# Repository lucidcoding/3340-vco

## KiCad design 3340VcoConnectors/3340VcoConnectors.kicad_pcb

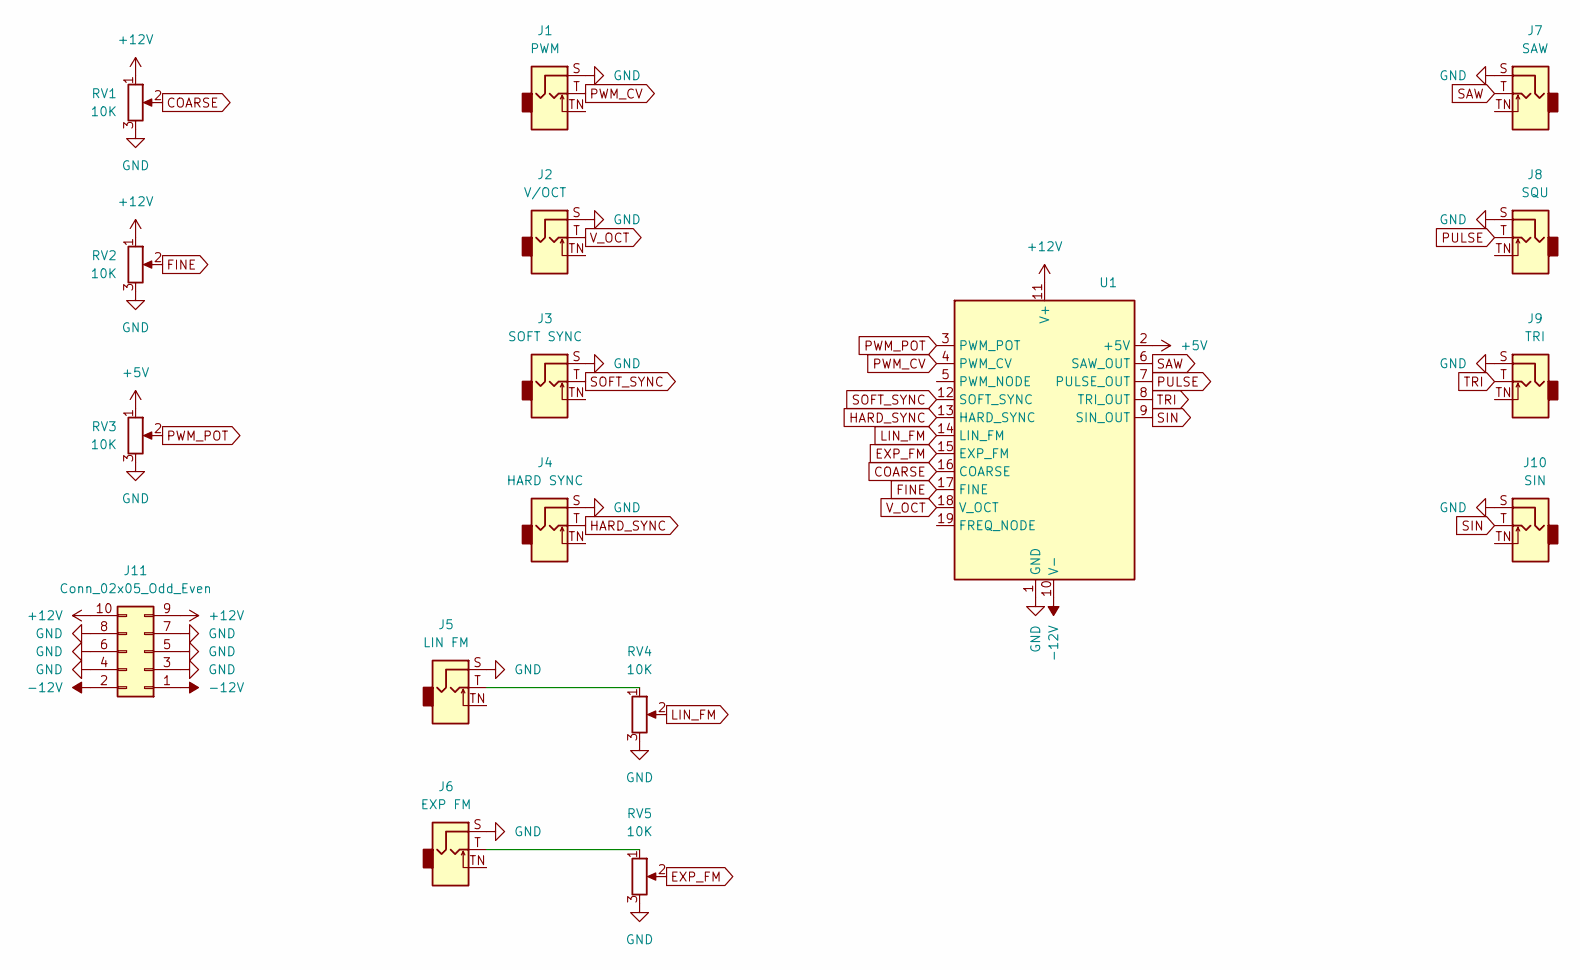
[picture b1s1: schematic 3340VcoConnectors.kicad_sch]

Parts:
J1: PWM; Jack_3.5mm_QingPu_WQP-PJ301M-12_Vertical
J2: V/OCT; Jack_3.5mm_QingPu_WQP-PJ301M-12_Vertical
J3: SOFT SYNC; Jack_3.5mm_QingPu_WQP-PJ301M-12_Vertical
J4: HARD SYNC; Jack_3.5mm_QingPu_WQP-PJ301M-12_Vertical
J5: LIN FM; Jack_3.5mm_QingPu_WQP-PJ301M-12_Vertical
J6: EXP FM; Jack_3.5mm_QingPu_WQP-PJ301M-12_Vertical
J7: SAW; Jack_3.5mm_QingPu_WQP-PJ301M-12_Vertical
J8: SQU; Jack_3.5mm_QingPu_WQP-PJ301M-12_Vertical
J9: TRI; Jack_3.5mm_QingPu_WQP-PJ301M-12_Vertical
J10: SIN; Jack_3.5mm_QingPu_WQP-PJ301M-12_Vertical
J11: Conn_02x05_Odd_Even; IDC-Header_2x05_P2.54mm_Vertical
RV1, RV2, RV3, RV4, RV5: 10K; RK097_Vertical
U1: Electrosmith_3340_VCO

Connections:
+5V: RV3.1, U1.2 (+5V)
+12V: J11.9, J11.10, RV1.1, RV2.1, U1.11 (V+)
-12V: J11.1, J11.2, U1.10 (V-)
COARSE: RV1.2, U1.16 (COARSE)
EXP_FM: RV5.2, U1.15 (EXP_FM)
FINE: RV2.2, U1.17 (FINE)
GND: J1.S, J2.S, J3.S, J4.S, J5.S, J6.S, J7.S, J8.S, J9.S, J10.S, J11.3, J11.4, J11.5, J11.6, J11.7, J11.8, RV1.3, RV2.3, RV3.3, RV4.3, RV5.3, U1.1 (GND)
HARD_SYNC: J4.T, U1.13 (HARD_SYNC)
LIN_FM: RV4.2, U1.14 (LIN_FM)
unnamed: J5.T, RV4.1
unnamed: J6.T, RV5.1
PULSE: J8.T, U1.7 (PULSE_OUT)
PWM_CV: J1.T, U1.4 (PWM_CV)
PWM_POT: RV3.2, U1.3 (PWM_POT)
SAW: J7.T, U1.6 (SAW_OUT)
SIN: J10.T, U1.9 (SIN_OUT)
SOFT_SYNC: J3.T, U1.12 (SOFT_SYNC)
TRI: J9.T, U1.8 (TRI_OUT)
V_OCT: J2.T, U1.18 (V_OCT)

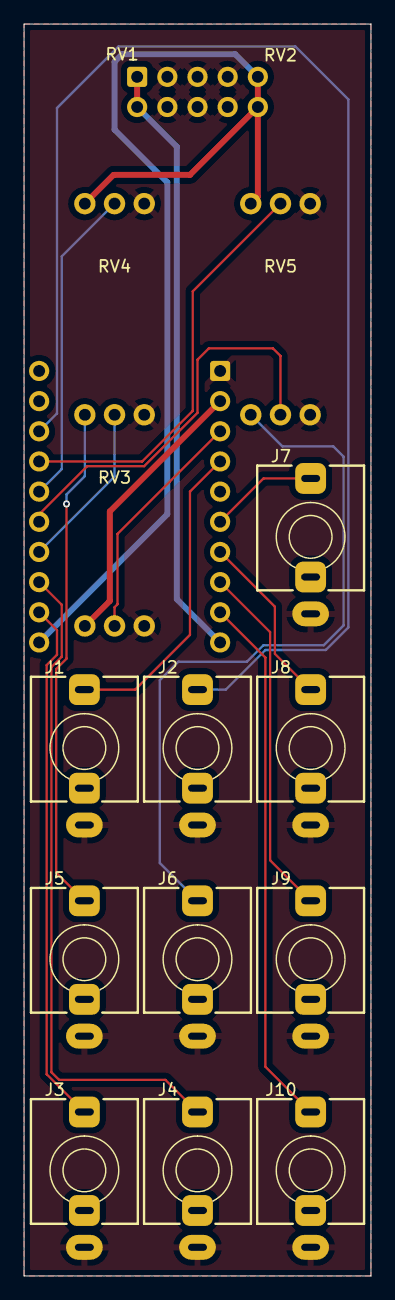
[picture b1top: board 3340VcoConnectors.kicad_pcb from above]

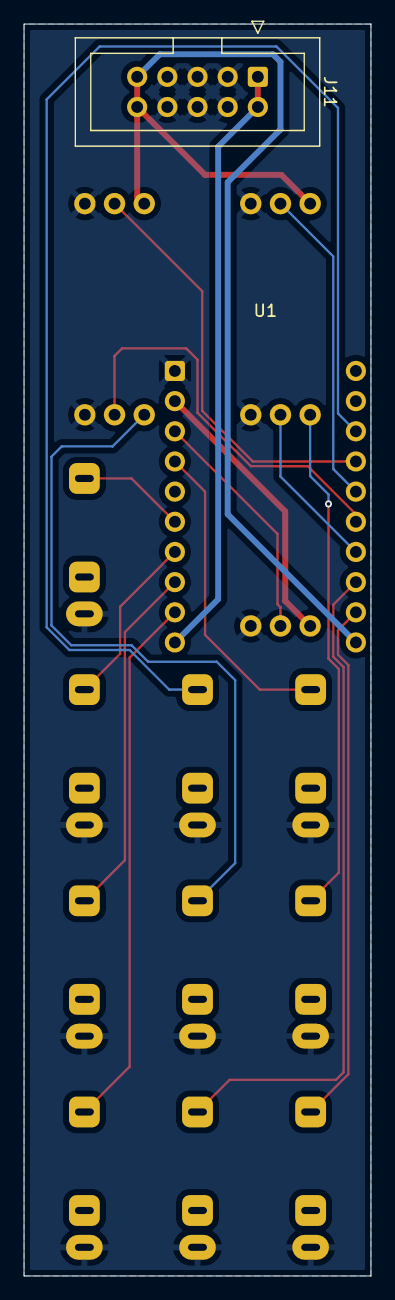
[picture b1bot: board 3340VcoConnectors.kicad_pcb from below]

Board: 2 copper layers, 29.2 x 105.4 mm, 17 parts (2 on the bottom side), 19 nets.

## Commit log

2025-06-16 Working version
